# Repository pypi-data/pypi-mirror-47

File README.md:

# PyPI code 47

This repo contains 40000 packages uploaded to PyPI between 
2019-05-28 10:31 and 2019-06-18 16:12.

The repo is 99% (39994/40000) complete.

Package contents can be found [in the code branch](https://github.com/pypi-data/pypi-mirror-47/tree/code/packages).

A browsable package list for all repositories [all packages here](https://pypi-data.github.io/website/repositories/pypi-mirror-47).

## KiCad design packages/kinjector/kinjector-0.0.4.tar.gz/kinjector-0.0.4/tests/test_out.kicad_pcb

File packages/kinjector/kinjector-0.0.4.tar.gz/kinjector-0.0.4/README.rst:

=========
KinJector
=========

.. image:: https://img.shields.io/pypi/v/kinjector.svg
        :target: https://pypi.python.org/pypi/kinjector

Inject/eject JSON/YAML data to/from KiCad Board files.

* Free software: MIT license
* Documentation: https://xesscorp.github.io/kinjector

Features
--------

* Parameters in one or more JSON or YAML files can be injected into a 
  KiCad PCB file.
* Parameters from a KiCad PCB file can be extracted and stored in a
  JSON or YAML file.
* The currently-supported set of parameters can control the design rules, net classes,
  assignment of netclasses to particular nets, plotting options,
  and (X,Y)/orientation/top-bottom-side position of part footprints.
* Subsets of parameters can be used to restrict the scope of effects upon the PCB.
* A script is provided to allow injection/ejection of JSON/YAML data to/from
  a KiCad PCB file. In addition, the ``kinjector`` module can be used within
  other Python scripts to manipulate KiCad PCB files.

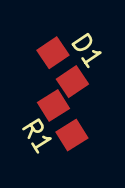
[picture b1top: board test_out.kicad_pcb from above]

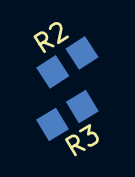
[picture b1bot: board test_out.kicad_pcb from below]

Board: 4 copper layers, 4 parts (2 on the bottom side), 4 nets, no tracks yet.

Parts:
D1: D; R_0805_2012Metric_Pad1.29x1.40mm_HandSolder
R1, R2, R3: R; R_0805_2012Metric_Pad1.29x1.40mm_HandSolder

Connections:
unnamed: D1.1, R1.1
unnamed: D1.2, R3.1
unnamed: R1.2, R2.2
unnamed: R2.1, R3.2

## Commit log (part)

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2023-08-06 Add package odoo12-addons-oca-server-tools/12.0.20190617.0/odoo12_addons_oca_server_tools-12.0.20190617.0-py3-none-any.whl
2023-08-06 Add package randomio2/0.1/randomio2-0.1.tar.gz
2023-08-06 Add package odoo8-addon-partner-street-number/8.0.1.0.0/odoo8_addon_partner_street_number-8.0.1.0.0-py2-none-any.whl
2023-08-06 Add package odoo10-addon-base-rest/10.0.2.0.0/odoo10_addon_base_rest-10.0.2.0.0-py2-none-any.whl
2023-08-06 Add package pushbroom/0.1.2/pushbroom-0.1.2.tar.gz
2023-08-06 Add package odoo10-addon-mail-check-mailbox-size/10.0.1.0.0.99.dev4/odoo10_addon_mail_check_mailbox_size-10.0.1.0.0.99.dev4-py2-none-any.whl
2023-08-06 Add package graphene-sqlalchemy/2.2.1/graphene_sqlalchemy-2.2.1-py2.py3-none-any.whl
2023-08-06 Add package pyflor/0.0.2a10/pyflor-0.0.2a10-py3-none-any.whl
2023-08-06 Add package http3/0.5.0/http3-0.5.0.tar.gz
2023-08-06 Add package odoo8-addon-account-draft-invoice-print/8.0.1.0.0.99.dev16/odoo8_addon_account_draft_invoice_print-8.0.1.0.0.99.dev16-py2-none-any.whl
2023-08-06 Add package odoo10-addon-account-mass-reconcile/10.0.1.0.0.99.dev21/odoo10_addon_account_mass_reconcile-10.0.1.0.0.99.dev21-py2-none-any.whl
2023-08-06 Add package validata-core/0.3.5/validata_core-0.3.5-py3-none-any.whl
2023-08-06 Add package oracle-version/0.0.8/oracle_version-0.0.8.tar.gz
2023-08-06 Add package validata-core/0.3.5/validata_core-0.3.5.tar.gz
2023-08-06 Add package nerus/1.4.0/nerus-1.4.0-py3-none-any.whl
2023-08-06 Add package odoo12-addon-website-blog-excerpt-img/12.0.1.0.0.99.dev2/odoo12_addon_website_blog_excerpt_img-12.0.1.0.0.99.dev2-py3-none-any.whl
2023-08-06 Add package odoo10-addon-partner-multi-relation/10.0.1.0.2.99.dev4/odoo10_addon_partner_multi_relation-10.0.1.0.2.99.dev4-py2-none-any.whl
2023-08-06 Add package odoo12-addon-account-payment-return-import-iso20022/12.0.1.0.1.99.dev1/odoo12_addon_account_payment_return_import_iso20022-12.0.1.0.1.99.dev1-py3-none-any.whl
2023-08-06 Add package odoo12-addon-account-banking-mandate/12.0.2.0.0.99.dev4/odoo12_addon_account_banking_mandate-12.0.2.0.0.99.dev4-py3-none-any.whl
2023-08-06 Add package odoo11-addon-account-asset-disposal/11.0.1.0.0.99.dev1/odoo11_addon_account_asset_disposal-11.0.1.0.0.99.dev1-py2.py3-none-any.whl
2023-08-06 Add package privex-helpers/1.0.1/privex_helpers-1.0.1-py3-none-any.whl
2023-08-06 Add package odoo12-addons-oca-partner-contact/12.0.20190617.0/odoo12_addons_oca_partner_contact-12.0.20190617.0-py3-none-any.whl
2023-08-06 Add package odoo11-addon-account-banking-mandate/11.0.2.0.0.99.dev4/odoo11_addon_account_banking_mandate-11.0.2.0.0.99.dev4-py2.py3-none-any.whl
2023-08-06 Add package mario/0.0.105/mario-0.0.105-py3-none-any.whl
2023-08-06 Add package odoo12-addon-l10n-it-vat-registries-split-payment/12.0.1.0.1/odoo12_addon_l10n_it_vat_registries_split_payment-12.0.1.0.1-py3-none-any.whl
2023-08-06 Add package yandexcloud/0.10.0/yandexcloud-0.10.0.tar.gz
2023-08-06 Add package DemoModule-pkg/0.1.0/DemoModule_pkg-0.1.0-py3-none-any.whl
2023-08-06 Add package odoo10-addon-partner-capital/10.0.1.0.0.99.dev20/odoo10_addon_partner_capital-10.0.1.0.0.99.dev20-py2-none-any.whl
2023-08-06 Add package pykson/0.9.4/pykson-0.9.4.tar.gz
2023-08-06 Add package gilly-utilities/0.9.6/gilly_utilities-0.9.6-py3-none-any.whl
2023-08-06 Add package creevey/1.4.2/creevey-1.4.2.tar.gz
2023-08-06 Add package odoo12-addon-base-rest/12.0.2.0.0/odoo12_addon_base_rest-12.0.2.0.0-py3-none-any.whl
2023-08-06 Add package lutils/0.6/lutils-0.6-py3-none-any.whl
2023-08-06 Add package tibia.py/2.1.0/tibia.py-2.1.0-py3-none-any.whl
2023-08-06 Add package gilly-utilities/0.9.6/gilly-utilities-0.9.6.tar.gz
2023-08-06 Add package recogym/0.1.1.0/recogym-0.1.1.0-py3-none-any.whl
2023-08-06 Add package symmetr/0.7.1/symmetr-0.7.1-py2-none-any.whl
2023-08-06 Add package ciscoaxl/0.0.21/ciscoaxl-0.0.21-py3-none-any.whl
2023-08-06 Add package mxnet-model-server/1.0.5b20190618/mxnet_model_server-1.0.5b20190618-py2.py3-none-any.whl
2023-08-06 Add package odoo11-addons-oca-stock-logistics-reporting/11.0.20190617.0/odoo11_addons_oca_stock_logistics_reporting-11.0.20190617.0-py2.py3-none-any.whl
2023-08-06 Add package odoo11-addon-base-rest-demo/11.0.2.0.0/odoo11_addon_base_rest_demo-11.0.2.0.0-py2.py3-none-any.whl
2023-08-06 Add package symmetr/0.7.0/symmetr-0.7.0-py3.6.egg
2023-08-06 Add package odoo12-addon-website-mass-mailing-name/12.0.1.0.0.99.dev1/odoo12_addon_website_mass_mailing_name-12.0.1.0.0.99.dev1-py3-none-any.whl
2023-08-06 Add package eloqua-lib/0.0.1/eloqua_lib-0.0.1-py3-none-any.whl
2023-08-06 Add package odds-client/0.16/odds_client-0.16-py3-none-any.whl
2023-08-06 Add package odoo10-addons-oca-social/10.0.20190617.0/odoo10_addons_oca_social-10.0.20190617.0-py2-none-any.whl
2023-08-06 Add package odoo12-addon-module-auto-update/12.0.2.0.5.99.dev4/odoo12_addon_module_auto_update-12.0.2.0.5.99.dev4-py3-none-any.whl
2023-08-06 Add package odoo12-addon-currency-rate-update/12.0.1.1.1.99.dev4/odoo12_addon_currency_rate_update-12.0.1.1.1.99.dev4-py3-none-any.whl
2023-08-06 Add package navec/0.5.0/navec-0.5.0-py2.py3-none-any.whl
2023-08-06 Add package odoo8-addon-l10n-de-country-states/8.0.1.0.0.99.dev5/odoo8_addon_l10n_de_country_states-8.0.1.0.0.99.dev5-py2-none-any.whl
2023-08-06 Add package pulumi-aws/0.18.11/pulumi_aws-0.18.11.tar.gz
2023-08-06 Add package urlextract/0.12.1/urlextract-0.12.1-py3-none-any.whl
2023-08-06 Add package wendelin.core/0.13/wendelin.core-0.13.tar.gz
2023-08-06 Add package staticfg/0.9.4/staticfg-0.9.4.tar.gz
2023-08-06 Add package pugnlp/0.2.3/pugnlp-0.2.3-py2.py3-none-any.whl
2023-08-06 Add package c2cwsgiutils/3.3.0/c2cwsgiutils-3.3.0-py3-none-any.whl
2023-08-06 Add package bilby/0.5.2/bilby-0.5.2.tar.gz
2023-08-06 Add package MatricesM/0.9a21/MatricesM-0.9a21-cp36-cp36m-win_amd64.whl
2023-08-06 Add package pycurious/0.3/pycurious-0.3.tar.gz
2023-08-06 Add package firex-flame-ui/0.20.2/firex_flame_ui-0.20.2.tar.gz
2023-08-06 Add package lepmlutils/2.0.11/lepmlutils-2.0.11.tar.gz
2023-08-06 Add package sel4-deps/0.2.4/sel4-deps-0.2.4.tar.gz
2023-08-06 Add package rosreestr-api/0.1.0/rosreestr-api-0.1.0.tar.gz
2023-08-06 Add package symmetr/0.7.2/symmetr-0.7.2-py2-none-any.whl
2023-08-06 Add package findabuse/0.1.4/findabuse-0.1.4.tar.gz
2023-08-06 Add package lipo2pol/0.0.2/lipo2pol-0.0.2-py3-none-any.whl
2023-08-06 Add package mkTranslation/1.0.0/mkTranslation-1.0.0-py3-none-any.whl
2023-08-06 Add package edinet-python/0.1.4/edinet-python-0.1.4.tar.gz
2023-08-06 Add package blotter/1.12/blotter-1.12-py3-none-any.whl
2023-08-06 Add package zlhawq/1.2.6/zlhawq-1.2.6.zip
2023-08-06 Add package quantx-sdk/0.1.6/quantx_sdk-0.1.6.tar.gz
2023-08-06 Add package symmetr/0.7.2/symmetr-0.7.2.tar.gz
2023-08-06 Add package lntime/1.0.8/lntime-1.0.8.zip
2023-08-06 Add package blotter/1.13/blotter-1.13-py3-none-any.whl
2023-08-06 Add package spiketoolkit/0.3.3/spiketoolkit-0.3.3.tar.gz
2023-08-06 Add package lauztat/1.1.6/lauztat-1.1.6.tar.gz
2023-08-06 Add package smm-wrapper/1.1.1/smm_wrapper-1.1.1.tar.gz
2023-08-06 Add package stockist/0.1.1/stockist-0.1.1.tar.gz
2023-08-06 Add package stockist/0.1.1/stockist-0.1.1-py2.py3-none-any.whl
2023-08-06 Add package cricpy/0.0.12/cricpy-0.0.12-py3-none-any.whl
2023-08-06 Add package zlairflow/1.1.3/zlairflow-1.1.3-py3-none-any.whl
2023-08-06 Add package behave-manners/0.7.5/behave_manners-0.7.5-py2.py3-none-any.whl
2023-08-06 Add package rosreestr-api/0.1.1/rosreestr_api-0.1.1-py3-none-any.whl
2023-08-06 Add package xyscript/0.2.5.7/xyscript-0.2.5.7.tar.gz
2023-08-06 Add package LIBTwinSVM/0.2.0/LIBTwinSVM-0.2.0-cp35-cp35m-win_amd64.whl
2023-08-06 Add package originstamp-client/1.0.3/originstamp_client-1.0.3-py3-none-any.whl
2023-08-06 Add package xnni/0.7.1/xnni-0.7.1-py3-none-manylinux1_x86_64.whl
2023-08-06 Add package sql-tools/0.1.5/sql_tools-0.1.5.tar.gz
2023-08-06 Add package ciscoaxl/0.0.23/ciscoaxl-0.0.23-py3-none-any.whl
2023-08-06 Add package odata1cw/0.0.1/odata1cw-0.0.1-py3-none-any.whl
2023-08-06 Add package LIBTwinSVM/0.2.0/LIBTwinSVM-0.2.0-cp37-cp37m-manylinux1_x86_64.whl
2023-08-06 Add package dltpy/0.3.4/dltpy-0.3.4.tar.gz
2023-08-06 Add package odata1cw/0.0.1/odata1cw-0.0.1.tar.gz
2023-08-06 Add package LIBTwinSVM/0.2.0/LIBTwinSVM-0.2.0-cp37-cp37m-win_amd64.whl
2023-08-06 Add package facebook-wda/0.3.0/facebook_wda-0.3.0-py2-none-any.whl
2023-08-06 Add package facebook-wda/0.3.0/facebook-wda-0.3.0.tar.gz
2023-08-06 Add package rjob/1.0/rjob-1.0.tar.gz
2023-08-06 Add package vmware-exporter/0.9.4/vmware_exporter-0.9.4-py3-none-any.whl
2023-08-06 Add package pytensors/0.10.0/pytensors-0.10.0-py3-none-any.whl
2023-08-06 Add package pypi-example/0.0.1/pypi_example-0.0.1.tar.gz
2023-08-06 Add package scenario-testing-tools/0.10/scenario_testing_tools-0.10-py3-none-any.whl
2023-08-06 Add package lauztat/1.1.2/lauztat-1.1.2-py3.7.egg
2023-08-06 Add package scenario-testing-tools/0.10/scenario-testing-tools-0.10.tar.gz
2023-08-06 Add package python-datamatrix/0.10.4/python-datamatrix-0.10.4.tar.gz
2023-08-06 Add package finntk/0.0.45/finntk-0.0.45.tar.gz
2023-08-06 Add package xyscript/0.2.5.8/xyscript-0.2.5.8.tar.gz
2023-08-06 Add package accretion-common/0.1.0/accretion_common-0.1.0.tar.gz
2023-08-06 Add package lura/0.3.4/lura-0.3.4-py3-none-any.whl
2023-08-06 Add package forecastlib/0.1.56/forecastlib-0.1.56-py3-none-any.whl
2023-08-06 Add package accretion-workers/0.1.0/accretion_workers-0.1.0-py2.py3-none-any.whl
2023-08-06 Add package zaailabcorelib/0.1.4/zaailabcorelib-0.1.4.tar.gz
2023-08-06 Add package catboost-dev/0.13.1.2434/catboost_dev-0.13.1.2434-cp27-none-win_amd64.whl
2023-08-06 Add package catboost-dev/0.13.1.2434/catboost_dev-0.13.1.2434-cp35-none-macosx_10_6_intel.macosx_10_9_intel.macosx_10_9_x86_64.macosx_10_10_intel.macosx_10_10_x86_64.whl
2023-08-06 Add package cloudfile/0.2.6/cloudfile-0.2.6.tar.gz
2023-08-06 Add package accretion-cli/0.1.0/accretion_cli-0.1.0-py2.py3-none-any.whl
2023-08-06 Add package rhea/0.4.9/rhea-0.4.9.tar.gz
2023-08-06 Add package pyscf/1.6.2/pyscf-1.6.2-cp27-cp27m-macosx_10_6_intel.macosx_10_9_intel.macosx_10_9_x86_64.macosx_10_10_intel.macosx_10_10_x86_64.whl
2023-08-06 Add package catboost-dev/0.13.1.2434/catboost_dev-0.13.1.2434-cp35-none-manylinux1_x86_64.whl
2023-08-06 Add package pyscf/1.6.2/pyscf-1.6.2-cp37-cp37m-macosx_10_6_intel.macosx_10_9_intel.macosx_10_9_x86_64.macosx_10_10_intel.macosx_10_10_x86_64.whl
2023-08-06 Add package m3-ui/2.0.8.8/m3-ui-2.0.8.8.tar.gz
2023-08-06 Add package arrdem.datalog/1.0.0/arrdem.datalog-1.0.0.tar.gz
2023-08-06 Add package pyscf/1.6.2/pyscf-1.6.2-cp34-cp34m-manylinux1_x86_64.whl
2023-08-06 Add package flaskmongorm/0.3.1/flaskmongorm-0.3.1-py3-none-any.whl
2023-08-06 Add package p2p-python/2.1.1/p2p_python-2.1.1.tar.gz
2023-08-06 Add package tap-annie/0.1.6/tap-annie-0.1.6.tar.gz
2023-08-06 Add package tap-annie/0.1.6/tap_annie-0.1.6-py3-none-any.whl
2023-08-06 Add package keios-protocol-pocketsphinx/0.1.0/keios_protocol_pocketsphinx-0.1.0-py3-none-any.whl
2023-08-06 Add package mocpy/0.6.1/MOCPy-0.6.1-cp37-cp37m-manylinux1_i686.whl
2023-08-06 Add package privex-helpers/1.0.2/privex_helpers-1.0.2.tar.gz
2023-08-06 Add package catboost-dev/0.13.1.2434/catboost_dev-0.13.1.2434-cp37-none-win_amd64.whl
2023-08-06 Add package JAQK/0.0.2.2.3/JAQK-0.0.2.2.3-py3-none-any.whl
2023-08-06 Add package cond-rnn/1.3/cond_rnn-1.3-py2.py3-none-any.whl
2023-08-06 Add changes
2023-08-06 Add package clasp/0.2.7/clasp-0.2.7.tar.gz
2023-08-06 Add package netrd/0.1.1/netrd-0.1.1.tar.gz
2023-08-06 Add package price-parser/0.2.3/price-parser-0.2.3.tar.gz
2023-08-06 Add package price-parser/0.2.3/price_parser-0.2.3-py2.py3-none-any.whl
2023-08-06 Add package oci/2.2.14/oci-2.2.14-py2.py3-none-any.whl
2023-08-06 Add package kafka-avro-binary-consumer/0.0.0.1/kafka_avro_binary_consumer-0.0.0.1-py3-none-any.whl
2023-08-06 Add package cricpy/0.0.12/cricpy-0.0.12.tar.gz
2023-08-06 Add package nanowire-flask/0.0.111/nanowire_flask-0.0.111.tar.gz
2023-08-06 Add package ChiantiPy/0.8.6/ChiantiPy-0.8.6.tar.gz
2023-08-06 Add package pythreejs/2.1.0/pythreejs-2.1.0-py2.py3-none-any.whl
2023-08-06 Add package replay-trajectory-classification/0.5.4.dev0/replay_trajectory_classification-0.5.4.dev0-py3-none-any.whl
2023-08-06 Add package gcp-docuploader/2019.6.18/gcp_docuploader-2019.6.18-py3-none-any.whl
